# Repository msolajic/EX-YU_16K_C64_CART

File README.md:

# EX-YU_16K_C64_CART
16k Cartridge for the Commodore 64

See more here:
https://blog.8bitchip.info/141-dissecting-ex-yugoslavian-c64-cartridges-part-2/

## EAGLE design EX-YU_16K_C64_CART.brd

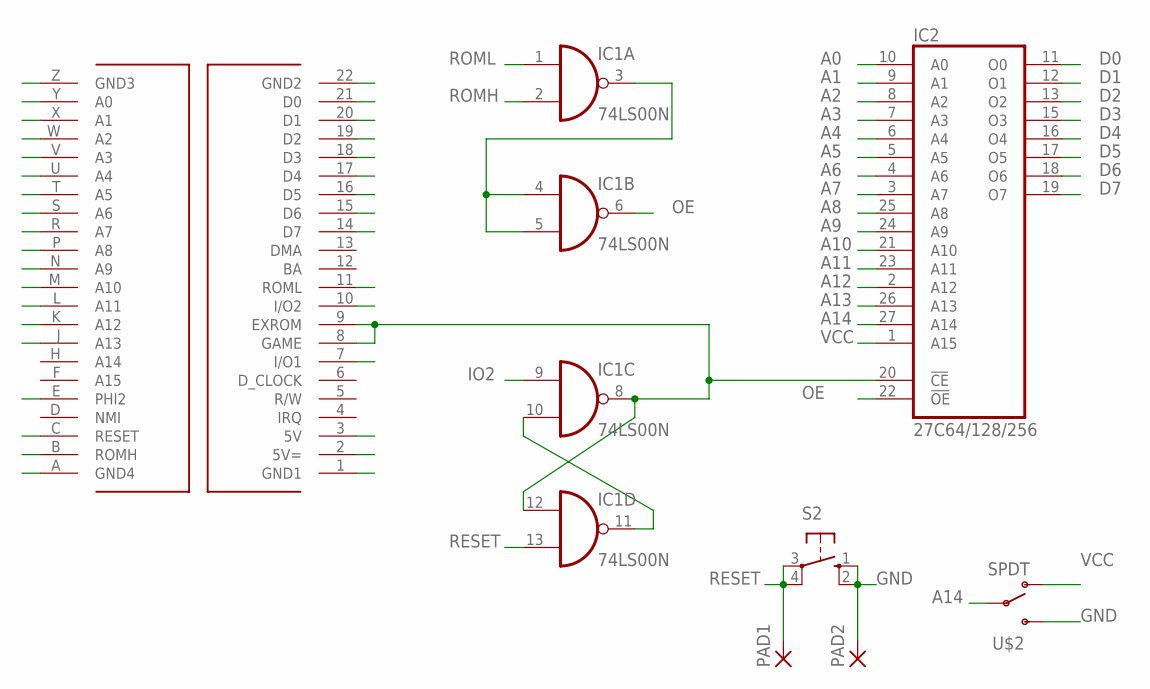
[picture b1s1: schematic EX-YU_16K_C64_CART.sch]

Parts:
IC1: 74LS00N; DIL14
IC2: 27C64/128/256; DIL28
PAD1, PAD2: SMD5; SMD2,54-5,08
S2: 10-XX; B3F-10XX
U$1: C64_EXPANSION__CARTRIDGE
U$2: SPDT; SPDT-SLIDE

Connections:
A0: IC2.10 (A0), U$1.Y (A0)
A1: IC2.9 (A1), U$1.X (A1)
A2: IC2.8 (A2), U$1.W (A2)
A3: IC2.7 (A3), U$1.V (A3)
A4: IC2.6 (A4), U$1.U (A4)
A5: IC2.5 (A5), U$1.T (A5)
A6: IC2.4 (A6), U$1.S (A6)
A7: IC2.3 (A7), U$1.R (A7)
A8: IC2.25 (A8), U$1.P (A8)
A9: IC2.24 (A9), U$1.N (A9)
A10: IC2.21 (A10), U$1.M (A10)
A11: IC2.23 (A11), U$1.L (A11)
A12: IC2.2 (A12), U$1.K (A12)
A13: IC2.26 (A13), U$1.J (A13)
A14: IC2.27 (A14), U$2.2
D0: IC2.11 (O0), U$1.21 (D0)
D1: IC2.12 (O1), U$1.20 (D1)
D2: IC2.13 (O2), U$1.19 (D2)
D3: IC2.15 (O3), U$1.18 (D3)
D4: IC2.16 (O4), U$1.17 (D4)
D5: IC2.17 (O5), U$1.16 (D5)
D6: IC2.18 (O6), U$1.15 (D6)
D7: IC2.19 (O7), U$1.14 (D7)
GND: IC1.7 (GND), IC2.14 (GND), PAD2.1, S2.1 (S), S2.2 (S1), U$1.1 (GND1), U$1.22 (GND2), U$1.A (GND4), U$1.Z (GND3), U$2.3
IO1: U$1.7 (I/O1)
IO2: IC1.9 (I0), U$1.10 (I/O2)
unnamed: IC1.3 (O), IC1.4 (I0), IC1.5 (I1)
unnamed: IC1.10 (I1), IC1.11 (O)
unnamed: IC1.8 (O), IC1.12 (I0), IC2.20 (!CE), U$1.8 (GAME), U$1.9 (EXROM)
OE: IC1.6 (O), IC2.22 (!OE)
PHI2: U$1.E (PHI2)
RESET: IC1.13 (I1), PAD1.1, S2.3, S2.4 (P1), U$1.C (RESET)
ROMH: IC1.2 (I1), U$1.B (ROMH)
ROML: IC1.1 (I0), U$1.11 (ROML)
VCC: IC1.14 (VCC), IC2.1 (A15), IC2.28 (VCC), U$1.2 (5V=), U$1.3 (5V), U$2.1

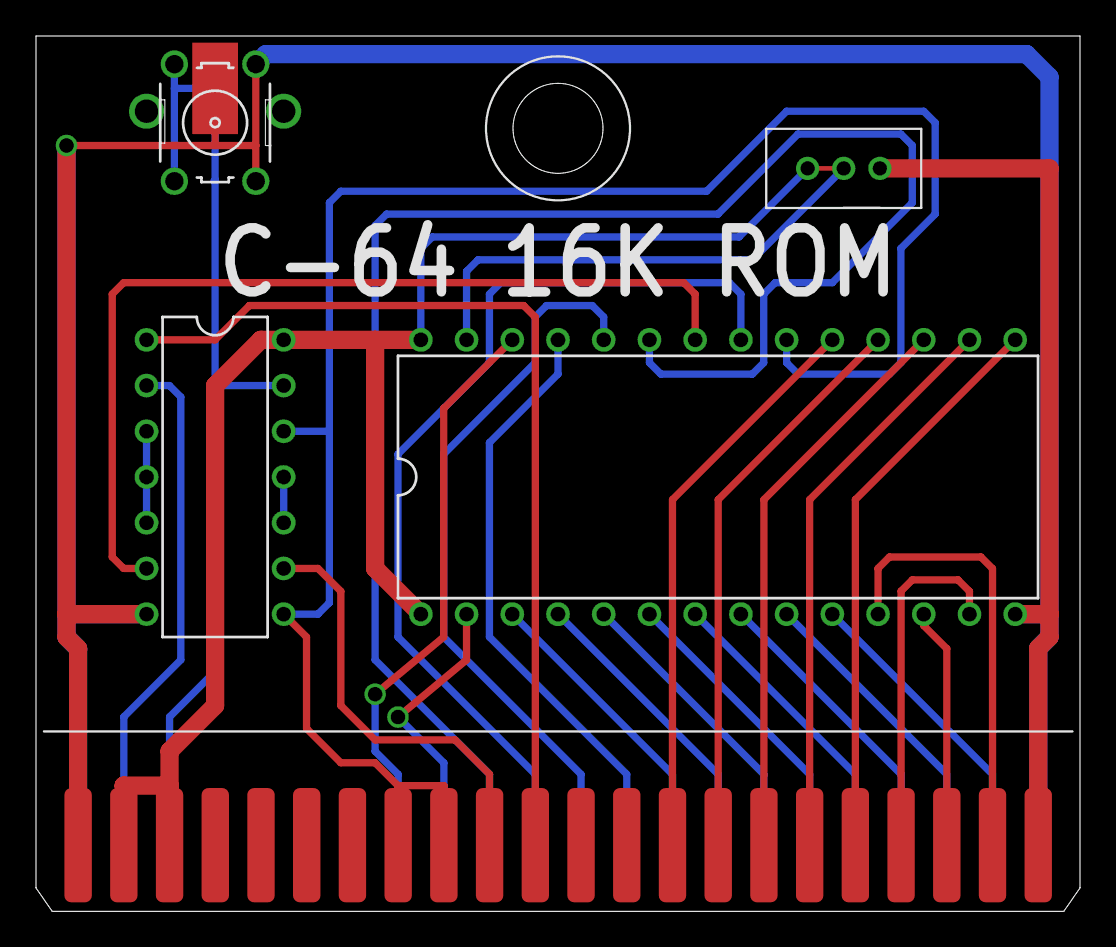
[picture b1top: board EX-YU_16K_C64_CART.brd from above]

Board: 2 copper layers, 58.0 x 48.6 mm, 7 parts (1 on the bottom side), 33 nets.
